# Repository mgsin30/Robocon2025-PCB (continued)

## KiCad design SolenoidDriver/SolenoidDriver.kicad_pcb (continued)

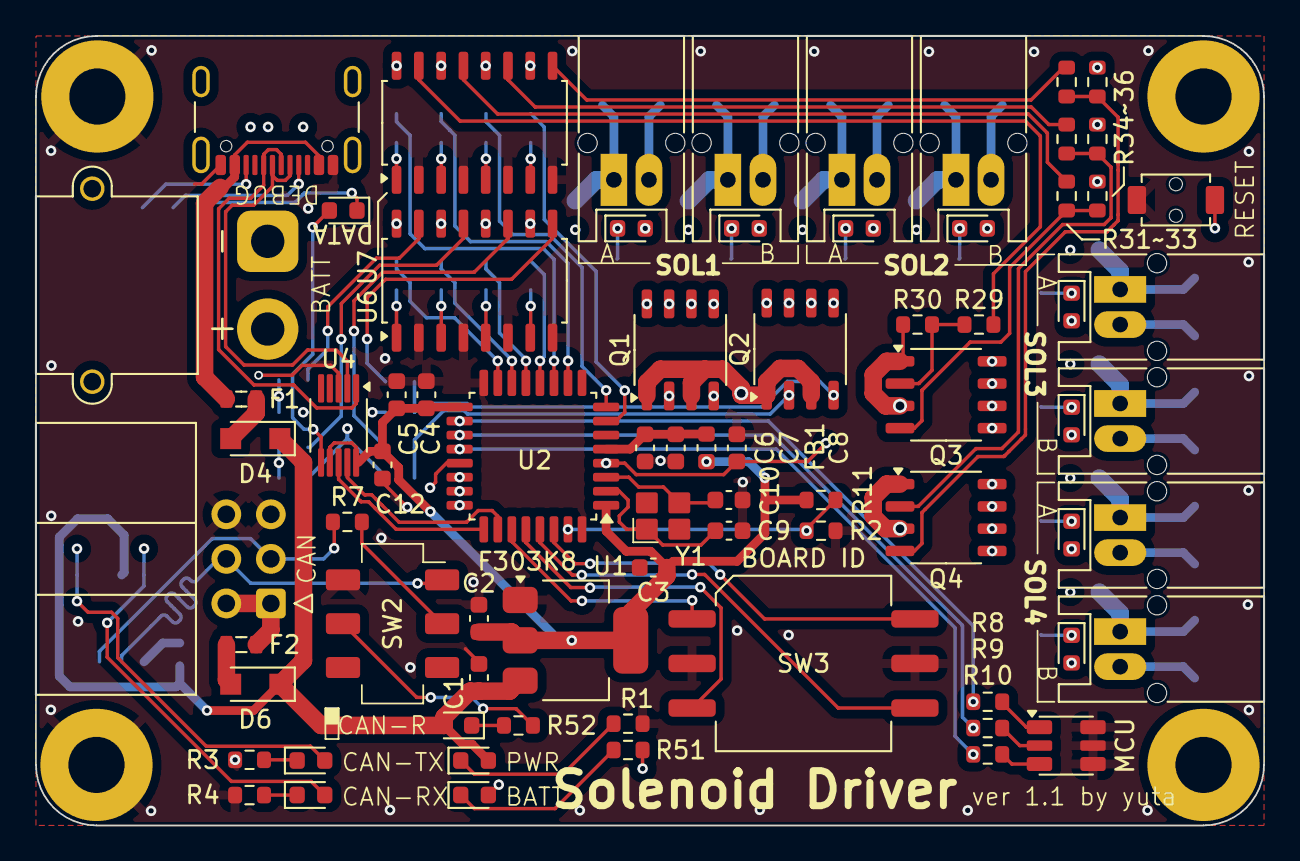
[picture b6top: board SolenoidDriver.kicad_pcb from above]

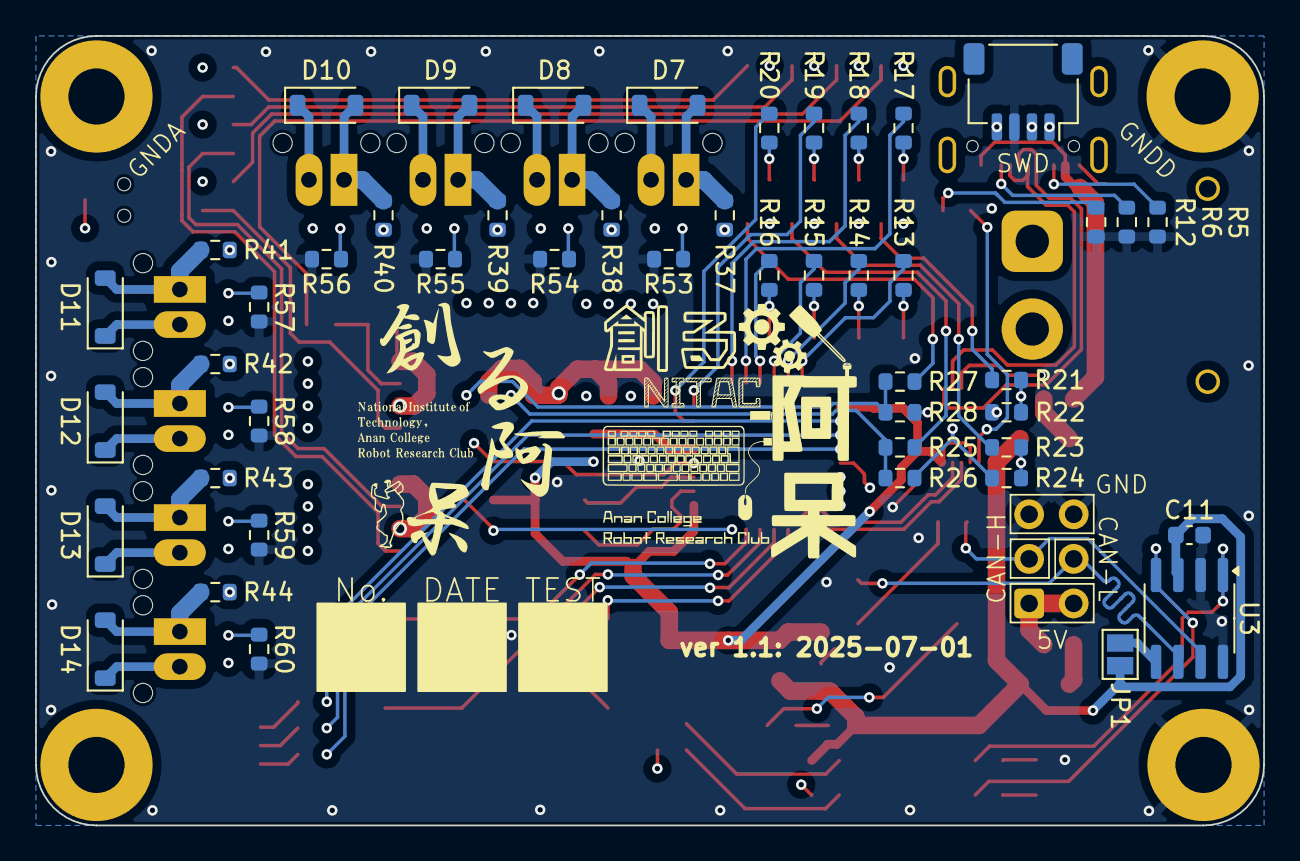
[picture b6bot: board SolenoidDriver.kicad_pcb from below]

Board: 4 copper layers, 70.0 x 45.0 mm, 129 parts (50 on the bottom side), 102 nets.

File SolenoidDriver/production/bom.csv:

Designator,Footprint,Quantity,Value,LCSC Part #
"C1, C2, C5",0603,3,4.7u,
"C10, C9",0603,2,15p,
"C11, C12, C3, C4, C6, C8",0603,6,0.1u,
C7,0603,1,1u,
"D1, D15",0603,2,LED,
"D10, D11, D12, D13, D14, D7, D8, D9",D_SOD-123,8,D,
D16,0603,1,SOL1A,
D17,0603,1,SOL1B,
D18,0603,1,SOL2A,
D19,0603,1,SOL2B,
D2,0603,1,CAN_TX,
D20,0603,1,SOL3A,
D21,0603,1,SOL3B,
D22,0603,1,SOL4A,
D23,0603,1,SOL4B,
D24,0603,1,CAN_R,
D3,0603,1,CAN_RX,
"D4, D6",Nexperia_CFP3_SOD-123W,2,D,
D5,0603,1,Data,
"F1, F2",MF-FSMF,2,Polyfuse,
FB1,0603,1,FerriteBead,
J1,JST_SH_SM04B-SRSS-TB_1x04-1MP_P1.00mm_Horizontal,1,SWD,
J10,PAコネクタ(2ピンサイド型),1,SOL4A,
J11,PAコネクタ(2ピンサイド型),1,SOL4B,
J12,AMASS_XT30PW-M_1x02_P2.50mm_Horizontal,1,BATT,
J2,USB_C_Receptacle_GCT_USB4105-xx-A_16P_TopMnt_Horizontal,1,Debug,
J3,IDC-Header_2x03_P2.54mm_Horizontal,1,CAN,
J4,PAコネクタ(2ピンサイド型),1,SOL1A,
J5,PAコネクタ(2ピンサイド型),1,SOL1B,
J6,PAコネクタ(2ピンサイド型),1,SOL2A,
J7,PAコネクタ(2ピンサイド型),1,SOL2B,
J8,PAコネクタ(2ピンサイド型),1,SOL3A,
J9,PAコネクタ(2ピンサイド型),1,SOL3B,
"Q1, Q2, Q3, Q4",Infineon_PG-DSO-8-24_4x5mm,4,Q_Dual_NMOS,
R1,0603,1,430,
R10,0603,1,300,
"R11, R2, R22, R24, R26, R28, R30, R34, R35, R36",0603,10,10k,
"R12, R3, R4",0603,3,96,
"R13, R14, R15, R16, R17, R18, R19, R20",0603,8,205,
"R21, R23, R25, R27, R29, R31, R32, R33",0603,8,50,
"R37, R38, R39, R40, R41, R42, R43, R44",0603,8,20,
"R5, R6",0603,2,5.1k,
R51,0603,1,1.5k,
R52,0603,1,420,
"R53, R54, R55, R56, R57, R58, R59, R60",0603,8,80,
R7,0603,1,120,
R8,0603,1,100,
R9,0603,1,600,
SW1,TVAF06-A020B-R,1,Reset,
SW2,SLW,1,CAN_R,
SW3,RDS-1055-SMT,1,SW_Coded,
U1,SOT-223-3_TabPin2,1,TLV1117-33,
U2,LQFP-32_7x7mm_P0.8mm,1,STM32F303K8Tx,
U3,SOIC-8_3.9x4.9mm_P1.27mm,1,MCP2561/2FD,
U4,MSOP-10_3x3mm_P0.5mm,1,CH340E,
U5,LED_ROHM_SMLVN6,1,LED_GRB,
"U6, U7",SOIC-16_4.55x10.3mm_P1.27mm,2,TLP293-4,
Y1,XRCGB,1,Crystal_GND2,
